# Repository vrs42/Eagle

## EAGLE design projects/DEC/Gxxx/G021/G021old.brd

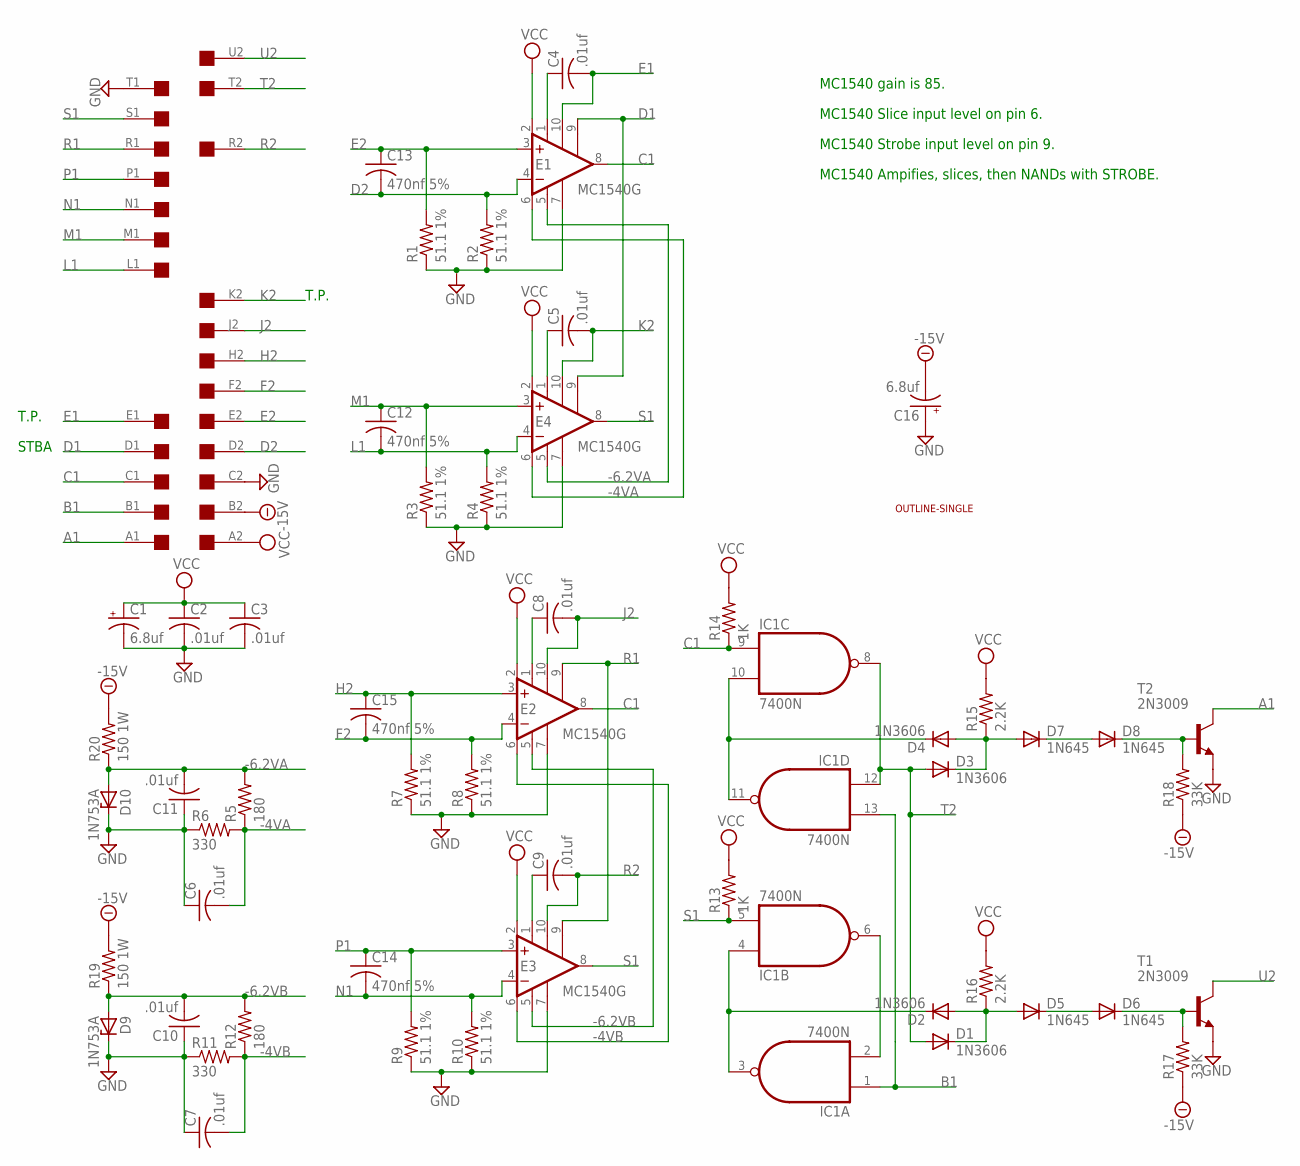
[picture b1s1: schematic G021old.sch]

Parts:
C1, C16: 6.8uf; E15-5
C2, C3, C4, C5, C6, C7, C8, C9, C10, C11: .01uf; C050-025X075
C12, C13, C14, C15: 470nf 5%; C050-025X075
D1, D2, D3, D4: 1N3606; DO35-10
D5, D6, D7, D8: 1N645; DO35-10
D9, D10: 1N753A; F126Z10
E1, E2, E3, E4: MC1540G; 602B
IC1: 7400N; DIL14
R1, R2, R3, R4, R7, R8, R9, R10: 51.1 1%; 0207/10
R5, R12: 180; 0207/10
R6, R11: 330; 0207/10
R13, R14: 1K; 0207/10
R15, R16: 2.2K; 0207/10
R17, R18: 33K; 0207/10
R19, R20: 150 1W; 0414/15
T1, T2: 2N3009; TO92
U$1: SINGLE; EDGE-CON2
U$2: OUTLINE-SINGLE; SINGLE

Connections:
-4VA: C6.2, E1.6 (SLICE), E4.6 (SLICE), R5.1, R6.2
-4VB: C7.2, E2.6 (SLICE), E3.6 (SLICE), R11.2, R12.1
-6.2VA: C11.2, D10.A, E1.5 (V-), E4.5 (V-), R5.2, R20.1
-6.2VB: C10.2, D9.A, E2.5 (V-), E3.5 (V-), R12.2, R19.1
-15V: C16.-, R17.1, R18.1, R19.2, R20.2, U$1.B2
A1: T2.1 (C), U$1.A1
B1: IC1.1 (I0), IC1.13 (I1), U$1.B1
C1: E1.8 (OUT), E2.8 (OUT), IC1.9 (I0), R14.1, U$1.C1
D1: E1.9 (ISTROBE), E4.9 (ISTROBE), U$1.D1
D2: C13.2, E1.4 (-IN), R2.2, U$1.D2
E1: C4.2, E1.10 (CEXTB), U$1.E1
E2: C13.1, E1.3 (+IN), R1.2, U$1.E2
F2: C15.2, E2.4 (-IN), R8.2, U$1.F2
GND: C1.-, C2.2, C3.2, C6.1, C7.1, C10.1, C11.1, C16.+, D9.C, D10.C, E1.7 (GND), E2.7 (GND), E3.7 (GND), E4.7 (GND), IC1.7 (GND), R1.1, R2.1, R3.1, R4.1, R6.1, R7.1, R8.1, R9.1, R10.1, R11.1, T1.3 (E), T2.3 (E), U$1.C2, U$1.T1
H2: C15.1, E2.3 (+IN), R7.2, U$1.H2
J2: C8.2, E2.10 (CEXTB), U$1.J2
K2: C5.2, E4.10 (CEXTB), U$1.K2
L1: C12.2, E4.4 (-IN), R4.2, U$1.L1
M1: C12.1, E4.3 (+IN), R3.2, U$1.M1
N1: C14.2, E3.4 (-IN), R10.2, U$1.N1
unnamed: C4.1, E1.1 (CEXTA)
unnamed: C8.1, E2.1 (CEXTA)
unnamed: C5.1, E4.1 (CEXTA)
unnamed: C9.1, E3.1 (CEXTA)
unnamed: D1.C, D2.A, D5.A, R16.1
unnamed: D4.C, IC1.10 (I1), IC1.11 (O)
unnamed: D2.C, IC1.3 (O), IC1.4 (I0)
unnamed: IC1.2 (I1), IC1.6 (O)
unnamed: D3.C, D4.A, D7.A, R15.1
unnamed: D7.C, D8.A
unnamed: D5.C, D6.A
unnamed: D8.C, R18.2, T2.2 (B)
unnamed: D6.C, R17.2, T1.2 (B)
P1: C14.1, E3.3 (+IN), R9.2, U$1.P1
R1: E2.9 (ISTROBE), E3.9 (ISTROBE), U$1.R1
R2: C9.2, E3.10 (CEXTB), U$1.R2
S1: E3.8 (OUT), E4.8 (OUT), IC1.5 (I1), R13.1, U$1.S1
T2: D1.A, D3.A, IC1.8 (O), IC1.12 (I0), U$1.T2
U2: T1.1 (C), U$1.U2
VCC: C1.+, C2.1, C3.1, E1.2 (V+), E2.2 (V+), E3.2 (V+), E4.2 (V+), IC1.14 (VCC), R13.2, R14.2, R15.2, R16.2, U$1.A2

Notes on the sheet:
T.P.
STBA
MC1540 gain is 85.
MC1540 Slice input level on pin 6.
MC1540 Strobe input level on pin 9.
MC1540 Ampifies, slices, then NANDs with STROBE.

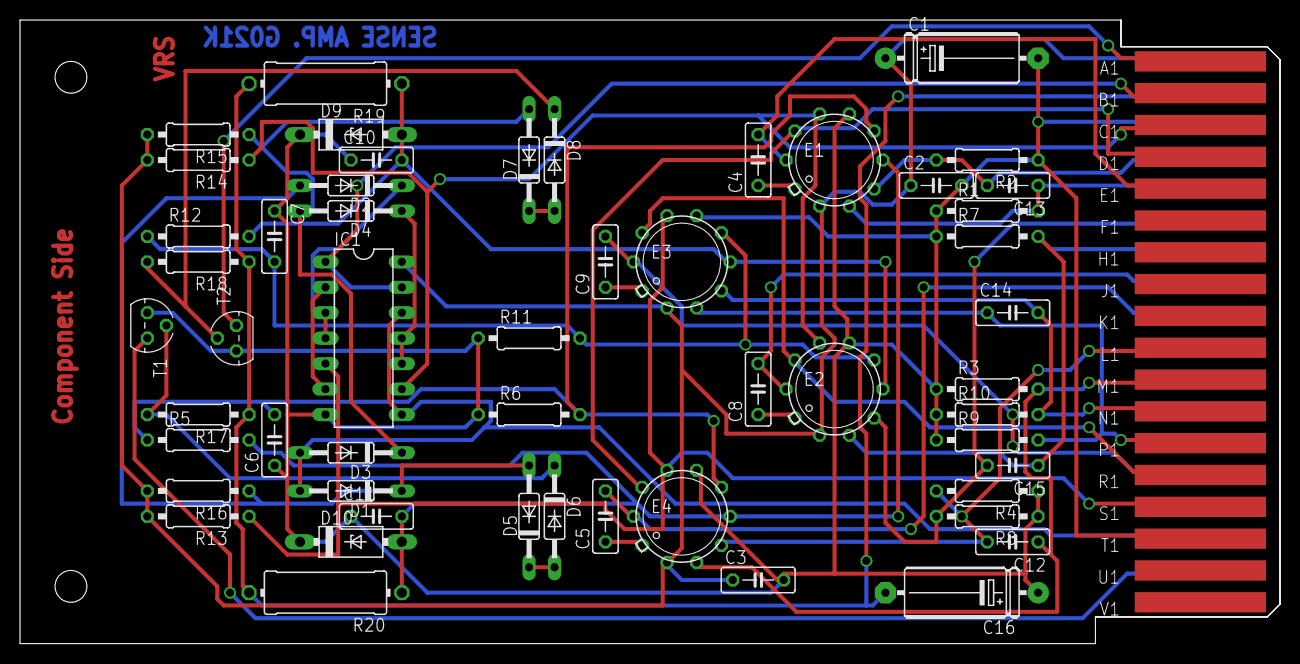
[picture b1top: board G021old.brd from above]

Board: 2 copper layers, 125.7 x 62.2 mm, 55 parts (0 on the bottom side), 40 nets.

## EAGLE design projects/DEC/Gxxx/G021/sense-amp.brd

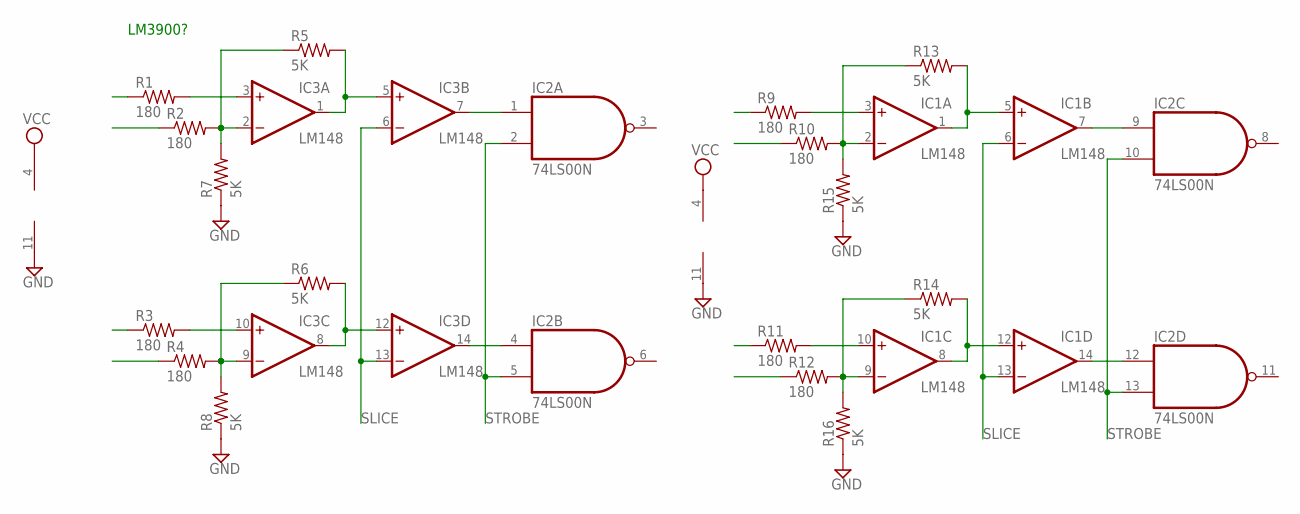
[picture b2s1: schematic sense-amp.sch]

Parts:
IC1, IC3: LM148; DIL14
IC2: 74LS00N; DIL14
R1, R2, R3, R4, R9, R10, R11, R12: 180; 0207/10
R5, R6, R7, R8, R13, R14, R15, R16: 5K; 0207/10

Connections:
GND: IC1.11 (V-), IC2.7 (GND), IC3.11 (V-), R7.1, R8.1, R15.1, R16.1
unnamed: IC3.8 (OUT), IC3.12 (+IN), R6.2
unnamed: IC3.1 (OUT), IC3.5 (+IN), R5.2
unnamed: IC3.9 (-IN), R4.2, R6.1, R8.2
unnamed: IC3.10 (+IN), R3.2
unnamed: IC3.2 (-IN), R2.2, R5.1, R7.2
unnamed: IC3.3 (+IN), R1.2
unnamed: IC1.8 (OUT), IC1.12 (+IN), R14.2
unnamed: IC1.1 (OUT), IC1.5 (+IN), R13.2
unnamed: IC1.9 (-IN), R12.2, R14.1, R16.2
unnamed: IC1.10 (+IN), R11.2
unnamed: IC1.2 (-IN), R10.2, R13.1, R15.2
unnamed: IC1.3 (+IN), R9.2
unnamed: IC2.1 (I0), IC3.7 (OUT)
unnamed: IC2.4 (I0), IC3.14 (OUT)
unnamed: IC1.14 (OUT), IC2.12 (I0)
unnamed: IC1.7 (OUT), IC2.9 (I0)
SLICE: IC1.6 (-IN), IC1.13 (-IN), IC3.6 (-IN), IC3.13 (-IN)
STROBE: IC2.2 (I1), IC2.5 (I1), IC2.10 (I1), IC2.13 (I1)
VCC: IC1.4 (V+), IC2.14 (VCC), IC3.4 (V+)

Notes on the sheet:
LM3900?

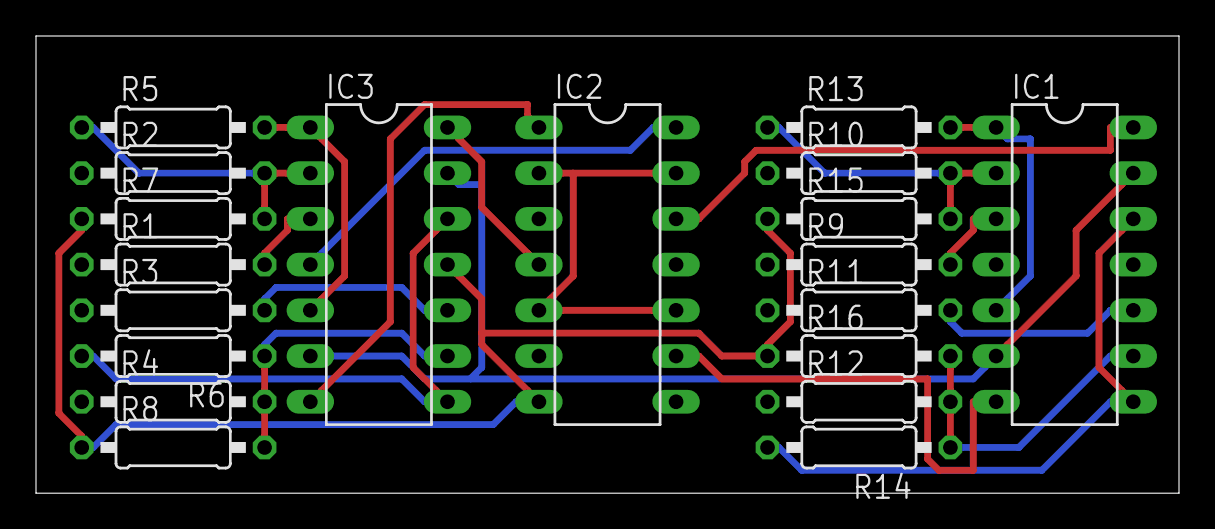
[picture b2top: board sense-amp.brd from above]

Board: 2 copper layers, 63.5 x 25.4 mm, 19 parts (0 on the bottom side), 20 nets.

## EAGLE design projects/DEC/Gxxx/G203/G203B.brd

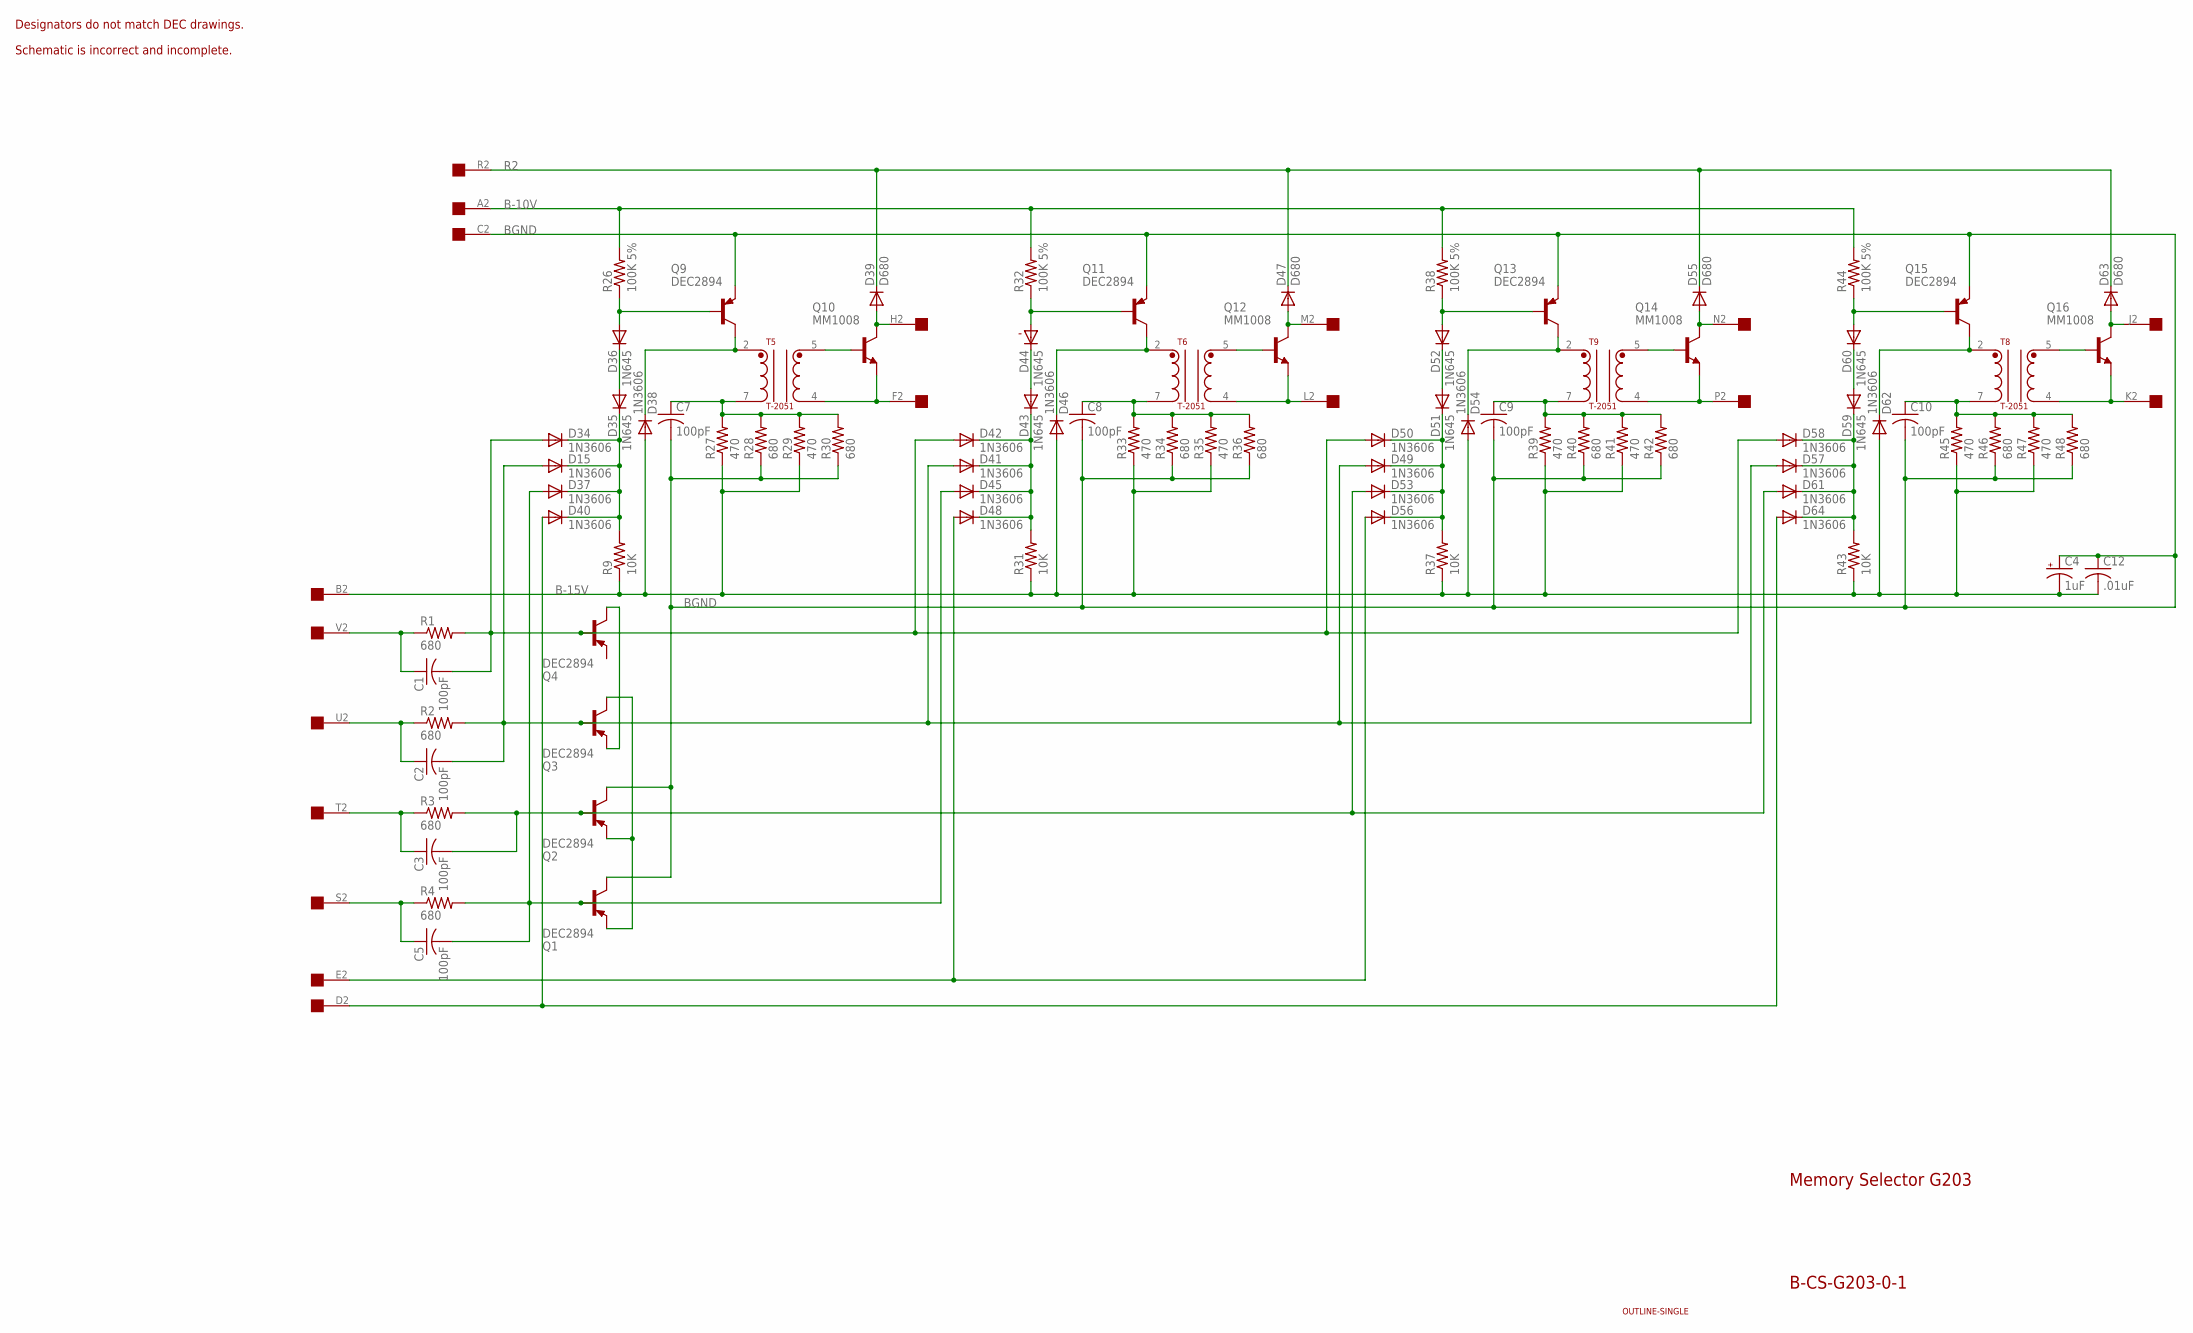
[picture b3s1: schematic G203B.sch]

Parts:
C1, C2, C3, C5, C7, C8, C9, C10: 100pF; C075-032X103
C4: 1uF; E12-4
C12: .01uF; C050-025X075
D15, D34, D37, D38, D40, D41, D42, D45, D46, D48, D49, D50, D53, D54, D56, D57, D58, D61, D62, D64: 1N3606; DO35-10
D35, D36, D43, D44, D51, D52, D59, D60: 1N645; DO35-10
D39, D47, D55, D63: D680; DO35-10
Q1, Q2, Q3, Q4, Q9, Q11, Q13, Q15: DEC2894; TO39
Q10, Q12, Q14, Q16: MM1008; TO5
R1, R2, R3, R4, R28, R30, R34, R36, R40, R42, R46, R48: 680; 0207/10
R9, R31, R37, R43: 10K; 0207/10
R26, R32, R38, R44: 100K 5%; 0207/10
R27, R29, R33, R35, R39, R41, R45, R47: 470; 0207/10
T5, T6, T8, T9: T-2051; TRANSFORMER
U$1: OUTLINE-SINGLE; SINGLE
U$2: EDGE-1; EDGE-CON1

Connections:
B-10V: R26.2, R32.2, R38.2, R44.2, U$2.A2
B-15V: C4.-, C12.2, D38.A, D46.A, D54.A, D62.A, R9.1, R27.1, R29.1, R31.1, R33.1, R35.1, R37.1, R39.1, R41.1, R43.1, R45.1, R47.1, U$2.B2
BGND: C4.+, C7.2, C8.2, C9.2, C10.2, C12.1, Q1.3 (C), Q2.3 (C), Q9.1 (E), Q11.1 (E), Q13.1 (E), Q15.1 (E), R28.1, R30.1, R34.1, R36.1, R40.1, R42.1, R46.1, R48.1, U$2.C2
D2: D40.A, D64.A, U$2.D2
E2: D48.A, D56.A, U$2.E2
F2: Q10.1 (E), T5.4, U$2.F2
H2: D39.A, Q10.3 (C), U$2.H2
J2: D63.A, Q16.3 (C), U$2.J2
K2: Q16.1 (E), T8.4, U$2.K2
L2: Q12.1 (E), T6.4, U$2.L2
M2: D47.A, Q12.3 (C), U$2.M2
N2: D55.A, Q14.3 (C), U$2.N2
unnamed: C8.1, R33.2, R34.2, R35.2, R36.2, T6.7
unnamed: C9.1, R39.2, R40.2, R41.2, R42.2, T9.7
unnamed: C1.2, D34.A, D42.A, D50.A, D58.A, Q4.2 (B), R1.2
unnamed: Q3.1 (E), Q4.3 (C)
unnamed: Q1.1 (E), Q2.1 (E), Q3.3 (C)
unnamed: C2.2, D15.A, D41.A, D49.A, D57.A, Q3.2 (B), R2.2
unnamed: C3.2, D53.A, D61.A, Q2.2 (B), R3.2
unnamed: C5.2, D37.A, D45.A, Q1.2 (B), R4.2
unnamed: D15.C, D34.C, D35.C, D37.C, D40.C, R9.2
unnamed: D35.A, D36.C
unnamed: D36.A, Q9.2 (B), R26.1
unnamed: D38.C, Q9.3 (C), T5.2
unnamed: C7.1, R27.2, R28.2, R29.2, R30.2, T5.7
unnamed: Q10.2 (B), T5.5
unnamed: D41.C, D42.C, D43.C, D45.C, D48.C, R31.2
unnamed: D43.A, D44.C
unnamed: D44.A, Q11.2 (B), R32.1
unnamed: D46.C, Q11.3 (C), T6.2
unnamed: Q12.2 (B), T6.5
unnamed: D49.C, D50.C, D51.C, D53.C, D56.C, R37.2
unnamed: D51.A, D52.C
unnamed: D52.A, Q13.2 (B), R38.1
unnamed: D54.C, Q13.3 (C), T9.2
unnamed: Q14.2 (B), T9.5
unnamed: D57.C, D58.C, D59.C, D61.C, D64.C, R43.2
unnamed: D59.A, D60.C
unnamed: D60.A, Q15.2 (B), R44.1
unnamed: D62.C, Q15.3 (C), T8.2
unnamed: C10.1, R45.2, R46.2, R47.2, R48.2, T8.7
unnamed: Q16.2 (B), T8.5
P2: Q14.1 (E), T9.4, U$2.P2
R2: D39.C, D47.C, D55.C, D63.C, U$2.R2
S2: C5.1, R4.1, U$2.S2
T2: C3.1, R3.1, U$2.T2
U2: C2.1, R2.1, U$2.U2
V2: C1.1, R1.1, U$2.V2

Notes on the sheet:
Memory Selector G203
B-CS-G203-0-1
Designators do not match DEC drawings.
Schematic is incorrect and incomplete.

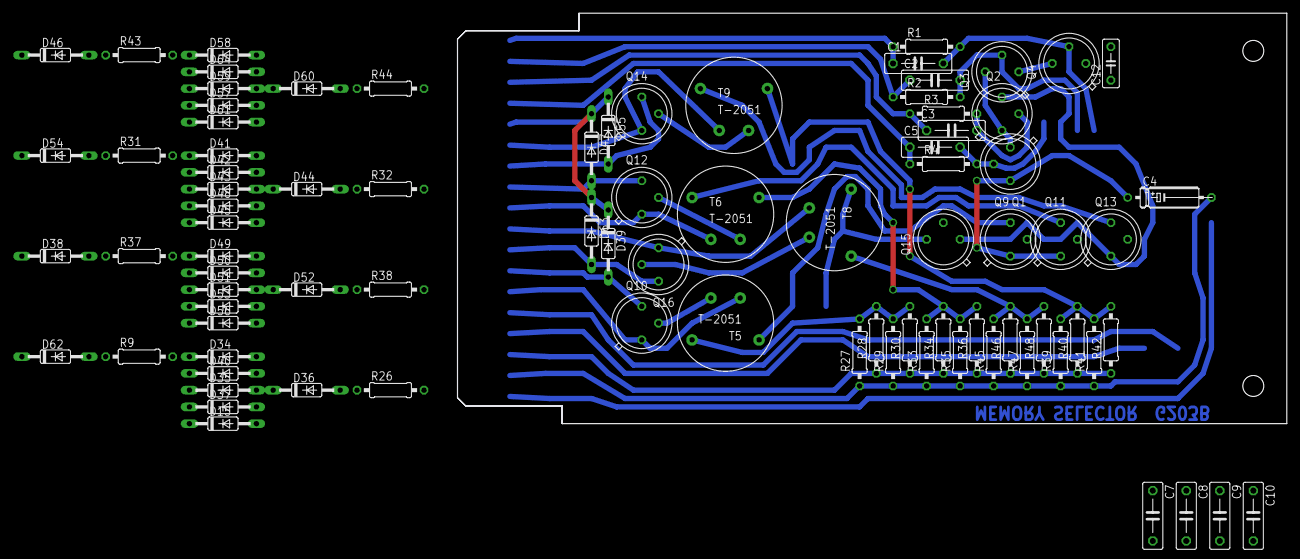
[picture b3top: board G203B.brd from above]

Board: 2 copper layers, 125.7 x 62.2 mm, 88 parts (0 on the bottom side), 48 nets.

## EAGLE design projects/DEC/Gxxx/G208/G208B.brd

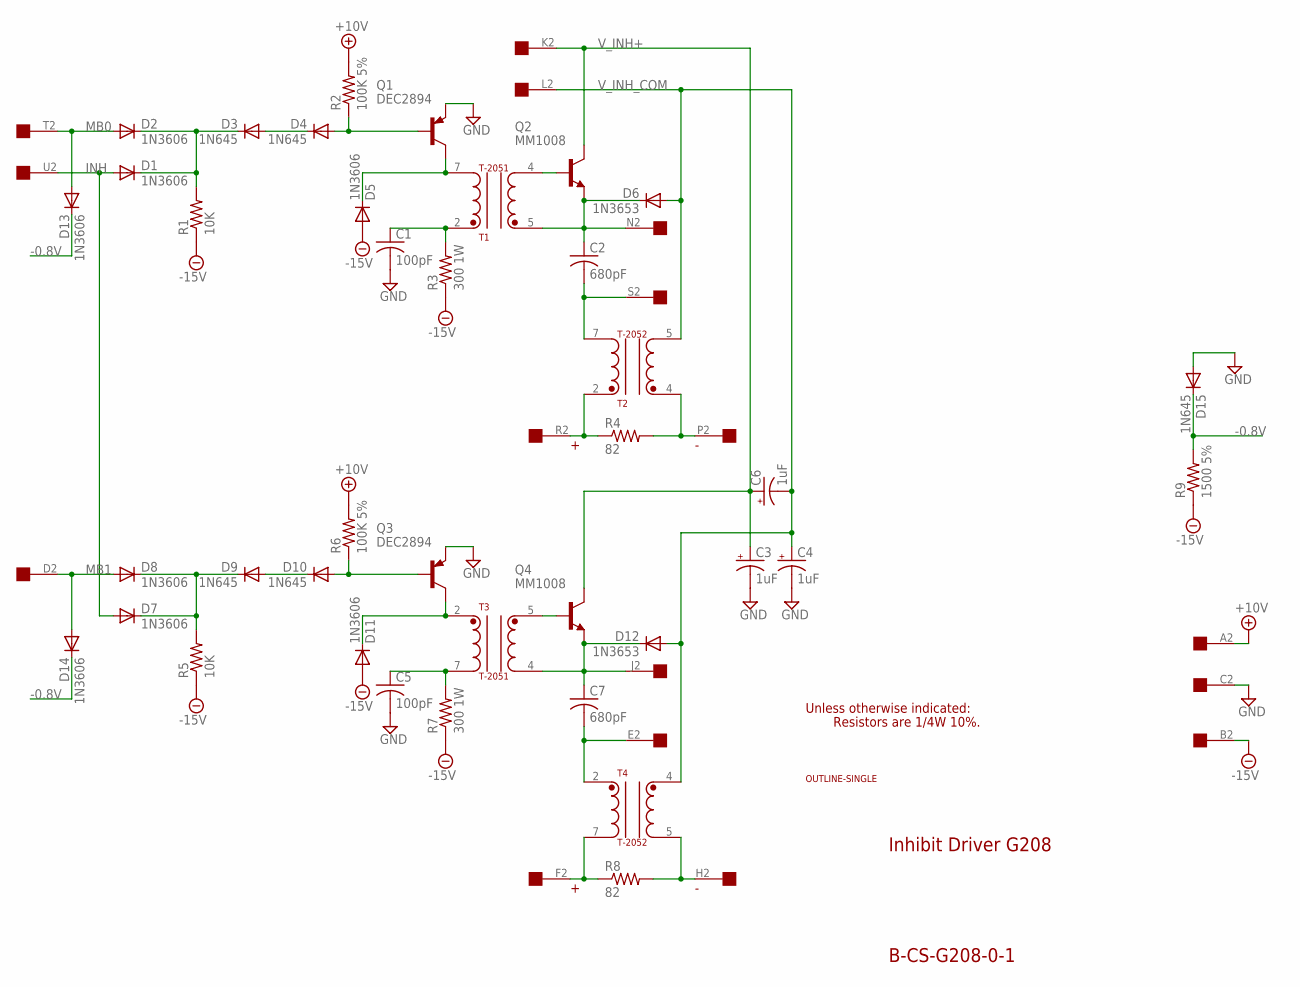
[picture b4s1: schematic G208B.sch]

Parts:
C1, C5: 100pF; C075-032X103
C2, C7: 680pF; C075-032X103
C3, C4, C6: 1uF; E25-9
D1, D2, D5, D7, D8, D11, D13, D14: 1N3606; DO35-10
D3, D4, D9, D10, D15: 1N645; DO35-10
D6, D12: 1N3653; DO35-10
Q1, Q3: DEC2894; TO39
Q2, Q4: MM1008; TO5
R1, R5: 10K; 0207/10
R2, R6: 100K 5%; 0207/10
R3, R7: 300 1W; 0617/22
R4, R8: 82; 0207/10
R9: 1500 5%; 0207/10
T1, T3: T-2051; TRANSFORMER
T2, T4: T-2052; TRANSFORMER
U$1: OUTLINE-SINGLE; SINGLE
U$2: EDGE-1; EDGE-CON1

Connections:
+10V: R2.2, R6.2, U$2.A2
-0.8V: D13.C, D14.C, D15.C, R9.2
-15V: D5.A, D11.A, R1.1, R3.1, R5.1, R7.1, R9.1, U$2.B2
GND: C1.2, C3.-, C4.-, C5.2, D15.A, Q1.1 (E), Q3.1 (E), U$2.C2
INH: D1.A, D7.A, U$2.U2
MB0: D2.A, D13.A, U$2.T2
MB1: D8.A, D14.A, U$2.D2
unnamed: D1.C, D2.C, D3.C, R1.2
unnamed: D3.A, D4.C
unnamed: D4.A, Q1.2 (B), R2.1
unnamed: D5.C, Q1.3 (C), T1.7
unnamed: C1.1, R3.2, T1.2
unnamed: Q2.2 (B), T1.4
unnamed: C2.1, D6.C, Q2.1 (E), T1.5, U$2.N2
unnamed: R4.1, T2.2, U$2.R2
unnamed: C2.2, T2.7, U$2.S2
unnamed: R4.2, T2.4, U$2.P2
unnamed: D7.C, D8.C, D9.C, R5.2
unnamed: D9.A, D10.C
unnamed: D10.A, Q3.2 (B), R6.1
unnamed: D11.C, Q3.3 (C), T3.2
unnamed: C5.1, R7.2, T3.7
unnamed: Q4.2 (B), T3.5
unnamed: C7.1, D12.C, Q4.1 (E), T3.4, U$2.J2
unnamed: C7.2, T4.2, U$2.E2
unnamed: R8.1, T4.7, U$2.F2
unnamed: R8.2, T4.5, U$2.H2
V_INH+: C3.+, C6.+, Q2.3 (C), Q4.3 (C), U$2.K2
V_INH_COM: C4.+, C6.-, D6.A, D12.A, T2.5, T4.4, U$2.L2

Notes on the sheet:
Inhibit Driver G208
B-CS-G208-0-1
Unless otherwise indicated:
Resistors are 1/4W 10%.

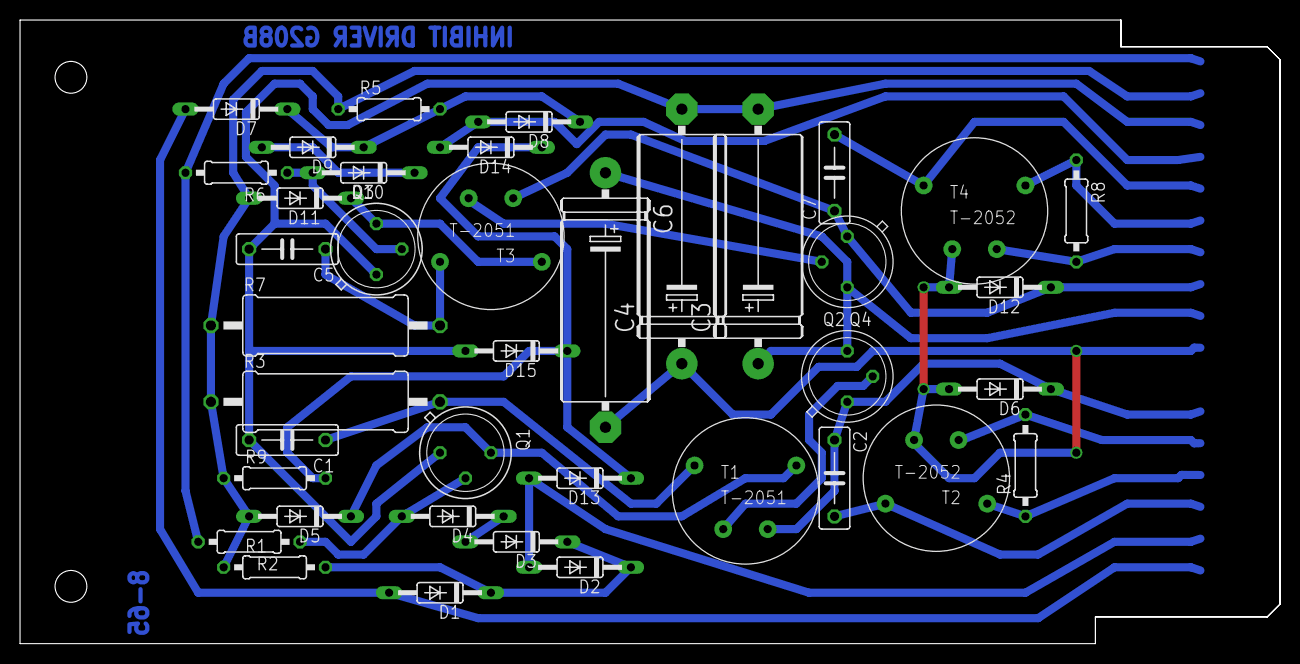
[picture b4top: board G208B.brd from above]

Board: 2 copper layers, 125.7 x 62.2 mm, 41 parts (0 on the bottom side), 29 nets.

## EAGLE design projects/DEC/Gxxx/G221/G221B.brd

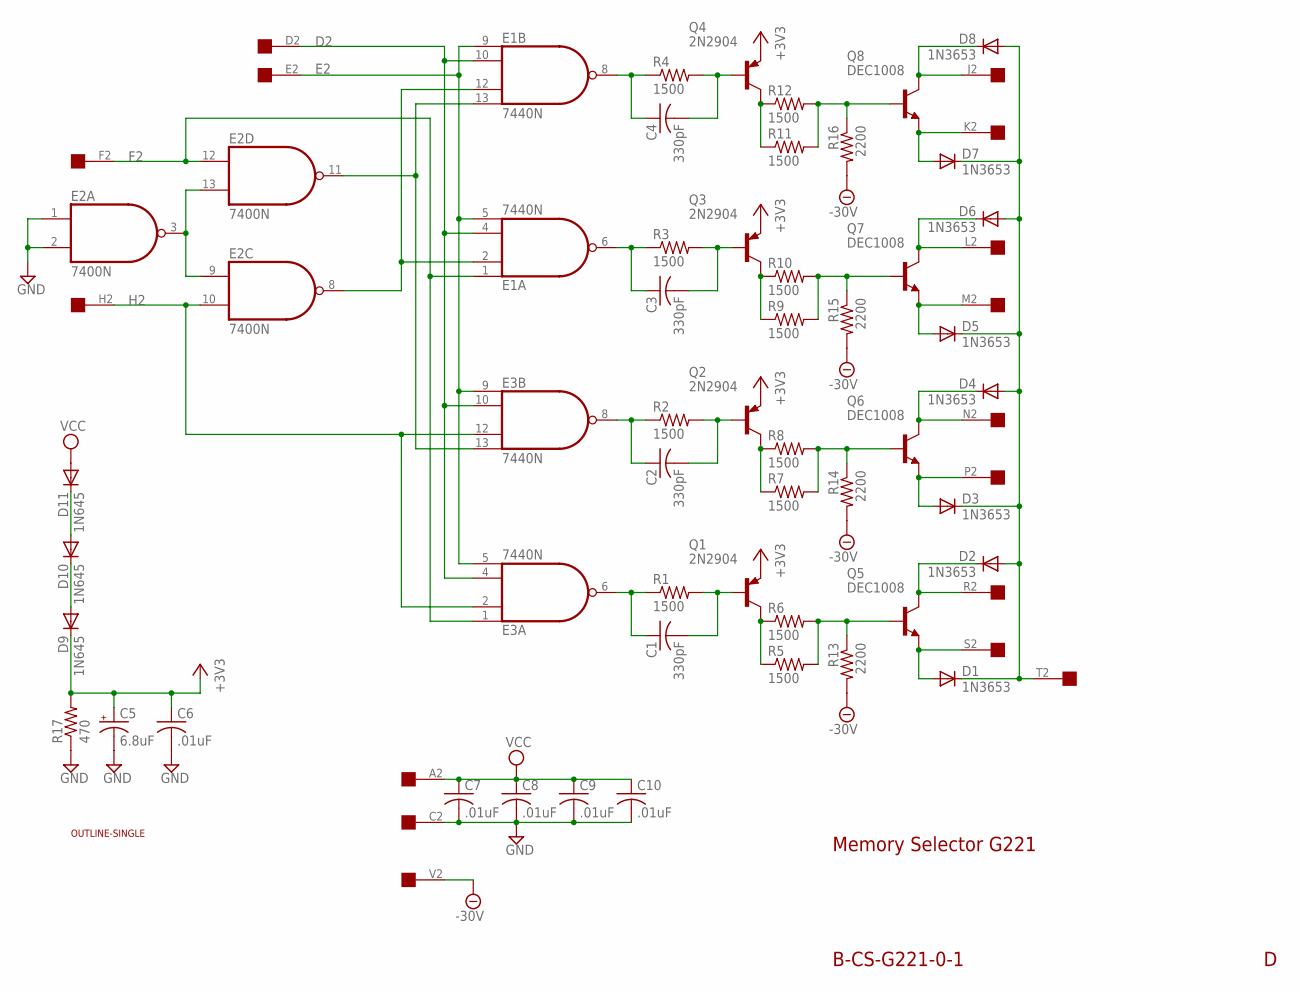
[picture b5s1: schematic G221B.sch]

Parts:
C1, C2, C3, C4: 330pF; C050-025X075
C5: 6.8uF; E12-8
C6, C7, C8, C9, C10: .01uF; C050-025X075
D1, D2, D3, D4, D5, D6, D7, D8: 1N3653; DO35-10
D9, D10, D11: 1N645; DO35-10
E1, E3: 7440N; DIL14
E2: 7400N; DIL14
Q1, Q2, Q3, Q4: 2N2904; TO39
Q5, Q6, Q7, Q8: DEC1008; TO39
R1, R2, R3, R4, R5, R6, R7, R8, R9, R10, R11, R12: 1500; 0207/10
R13, R14, R15, R16: 2200; 0207/10
R17: 470; 0207/10
U$1: EDGE-1; EDGE-CON1
U$7: OUTLINE-SINGLE; SINGLE

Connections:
+3V3: C5.+, C6.1, D9.C, Q1.1 (E), Q2.1 (E), Q3.1 (E), Q4.1 (E), R17.2
-24V: R13.2, R14.2, R15.2, R16.2, U$1.V2
D2: E1.4 (I2), E1.10 (I1), E3.4 (I2), E3.10 (I1), U$1.D2
E2: E1.5 (I3), E1.9 (I0), E3.5 (I3), E3.9 (I0), U$1.E2
F2: E1.1 (I0), E2.12 (I0), E3.1 (I0), U$1.F2
GND: C5.-, C6.2, C7.2, C8.2, C9.2, C10.2, E1.7 (GND), E2.1 (I0), E2.2 (I1), E2.7 (GND), E3.7 (GND), R17.1, U$1.C2
H2: E2.10 (I1), E3.2 (I1), E3.12 (I2), U$1.H2
J2: D8.C, Q8.3 (C), U$1.J2
K2: D7.A, Q8.1 (E), U$1.K2
L2: D6.C, Q7.3 (C), U$1.L2
M2: D5.A, Q7.1 (E), U$1.M2
N2: D4.C, Q6.3 (C), U$1.N2
unnamed: C1.1, E3.6 (O), R1.1
unnamed: Q1.3 (C), R5.1, R6.1
unnamed: Q5.2 (B), R5.2, R6.2, R13.1
unnamed: Q2.3 (C), R7.1, R8.1
unnamed: Q6.2 (B), R7.2, R8.2, R14.1
unnamed: E2.3 (O), E2.9 (I0), E2.13 (I1)
unnamed: C1.2, Q1.2 (B), R1.2
unnamed: C2.1, E3.8 (O), R2.1
unnamed: C2.2, Q2.2 (B), R2.2
unnamed: E1.13 (I3), E2.11 (O), E3.13 (I3)
unnamed: C3.1, E1.6 (O), R3.1
unnamed: E1.2 (I1), E1.12 (I2), E2.8 (O)
unnamed: C3.2, Q3.2 (B), R3.2
unnamed: D9.A, D10.C
unnamed: C4.1, E1.8 (O), R4.1
unnamed: D10.A, D11.C
unnamed: C4.2, Q4.2 (B), R4.2
unnamed: Q3.3 (C), R9.1, R10.1
unnamed: Q7.2 (B), R9.2, R10.2, R15.1
unnamed: Q4.3 (C), R11.1, R12.1
unnamed: Q8.2 (B), R11.2, R12.2, R16.1
P2: D3.A, Q6.1 (E), U$1.P2
R2: D2.C, Q5.3 (C), U$1.R2
S2: D1.A, Q5.1 (E), U$1.S2
T2: D1.C, D2.A, D3.C, D4.A, D5.C, D6.A, D7.C, D8.A, U$1.T2
VCC: C7.1, C8.1, C9.1, C10.1, D11.A, E1.14 (VCC), E2.14 (VCC), E3.14 (VCC), U$1.A2

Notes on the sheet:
B-CS-G221-0-1
Memory Selector G221

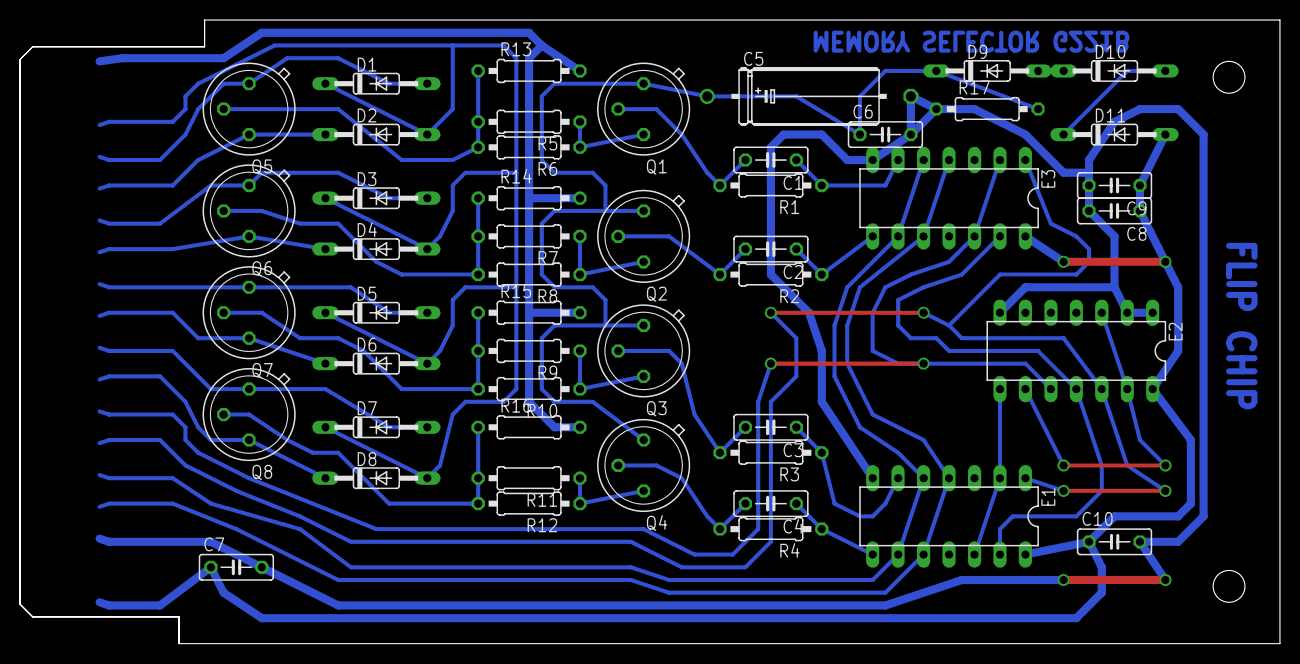
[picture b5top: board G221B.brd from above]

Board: 2 copper layers, 125.7 x 62.2 mm, 51 parts (0 on the bottom side), 38 nets.
